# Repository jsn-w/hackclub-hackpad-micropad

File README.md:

# micropad!
This is a 12-key 'macro'pad with an OLED display and LEDs underneath the keys!
I plan on using this as a numberpad, with extra keys (calculator, gamebar).

# Schematic and PCB!

<p>These were made in KiCad. There are two layers in this PCB. The top serves as the signal plane while the bottom serves as the ground plane.</p>

# CAD
</p>Here is the assembled piece within AutoDesk Fusion 360! I was unable to find 3D models for the LEDs. The microcontroller also wouldn't export to Fusion360. Below I attached the KiCad PCB model and the Fusion360 model.</p>

</p>I separated the model into two pieces to print.</p>

# Parts Used
| Quantity | Item                      |
|---------|----------------------------|
| 1       | XIAO RP2040                |
| 1       | 3D printed case: base      |
| 1       | 3D printed case: cap       |
| 9       | SK6812MINI LEDs            |
| 12      | Cherry MX Switches         |
| 12      | DSA Keycaps                |
| 1       | 0.91" 128x32 OLED Display  |

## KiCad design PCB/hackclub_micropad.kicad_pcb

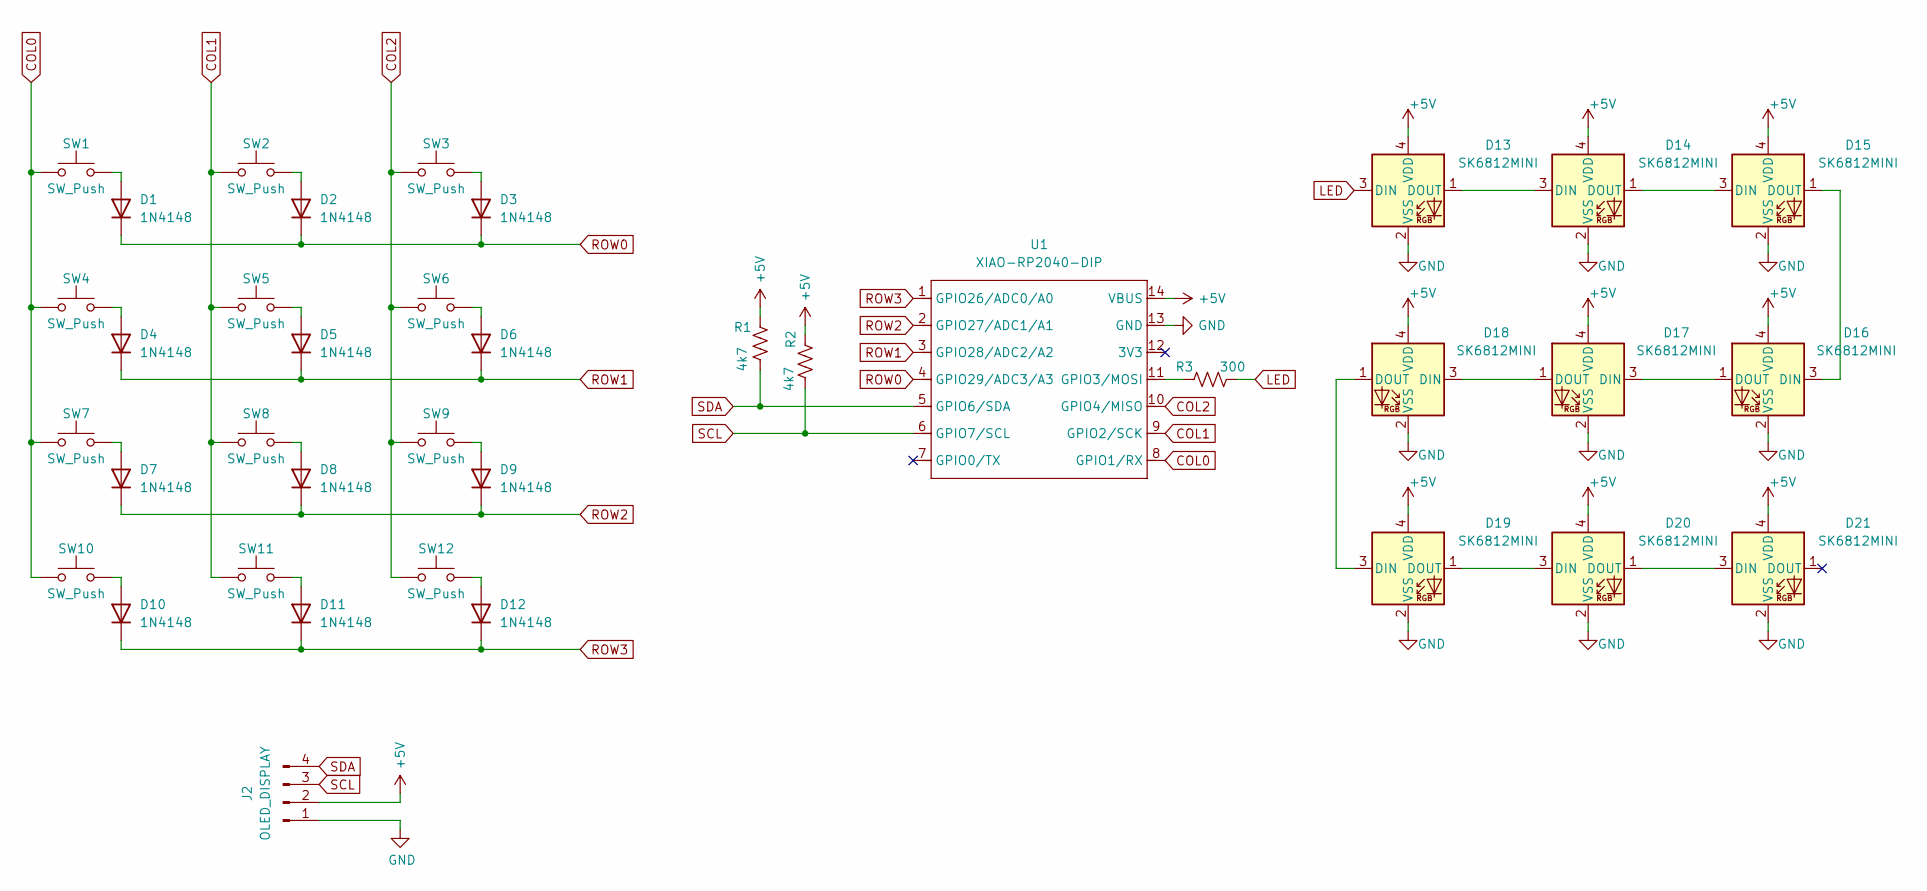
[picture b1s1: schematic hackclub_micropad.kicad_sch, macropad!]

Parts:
D1, D2, D3, D4, D5, D6, D7, D8, D9, D10, D11, D12: 1N4148; D_DO-35_SOD27_P7.62mm_Horizontal
D13, D14, D15, D16, D17, D18, D19, D20, D21: SK6812MINI; LED_SK6812MINI_PLCC4_3.5x3.5mm_P1.75mm
J2: OLED_DISPLAY; SSD1306-0.91-OLED-4pin-128x32
R1, R2: 4k7; R_0201_0603Metric_Pad0.64x0.40mm_HandSolder
R3: 300; R_0201_0603Metric_Pad0.64x0.40mm_HandSolder
SW1, SW2, SW3, SW4, SW5, SW6, SW7, SW8, SW9, SW10, SW11, SW12: SW_Push; SW_Cherry_MX_1.00u_PCB
U1: XIAO-RP2040-DIP

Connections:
+5V: D13.4 (VDD), D14.4 (VDD), D15.4 (VDD), D16.4 (VDD), D17.4 (VDD), D18.4 (VDD), D19.4 (VDD), D20.4 (VDD), D21.4 (VDD), J2.2, R1.1, R2.1, U1.14 (VBUS)
COL0: SW1.1, SW4.1, SW7.1, SW10.1, U1.8 (GPIO1/RX)
COL1: SW2.1, SW5.1, SW8.1, SW11.1, U1.9 (GPIO2/SCK)
COL2: SW3.1, SW6.1, SW9.1, SW12.1, U1.10 (GPIO4/MISO)
GND: D13.2 (VSS), D14.2 (VSS), D15.2 (VSS), D16.2 (VSS), D17.2 (VSS), D18.2 (VSS), D19.2 (VSS), D20.2 (VSS), D21.2 (VSS), J2.1, U1.13 (GND)
LED: D13.3 (DIN), R3.2
unnamed: D1.2 (A), SW1.2
unnamed: D2.2 (A), SW2.2
unnamed: D3.2 (A), SW3.2
unnamed: D4.2 (A), SW4.2
unnamed: D5.2 (A), SW5.2
unnamed: D6.2 (A), SW6.2
unnamed: D7.2 (A), SW7.2
unnamed: D8.2 (A), SW8.2
unnamed: D9.2 (A), SW9.2
unnamed: D10.2 (A), SW10.2
unnamed: D11.2 (A), SW11.2
unnamed: D12.2 (A), SW12.2
unnamed: D13.1 (DOUT), D14.3 (DIN)
unnamed: D14.1 (DOUT), D15.3 (DIN)
unnamed: D15.1 (DOUT), D16.3 (DIN)
unnamed: D16.1 (DOUT), D17.3 (DIN)
unnamed: D17.1 (DOUT), D18.3 (DIN)
unnamed: D18.1 (DOUT), D19.3 (DIN)
unnamed: D19.1 (DOUT), D20.3 (DIN)
unnamed: D20.1 (DOUT), D21.3 (DIN)
unnamed: R3.1, U1.11 (GPIO3/MOSI)
ROW0: D1.1 (K), D2.1 (K), D3.1 (K), U1.4 (GPIO29/ADC3/A3)
ROW1: D4.1 (K), D5.1 (K), D6.1 (K), U1.3 (GPIO28/ADC2/A2)
ROW2: D7.1 (K), D8.1 (K), D9.1 (K), U1.2 (GPIO27/ADC1/A1)
ROW3: D10.1 (K), D11.1 (K), D12.1 (K), U1.1 (GPIO26/ADC0/A0)
SCL: J2.3, R2.2, U1.6 (GPIO7/SCL)
SDA: J2.4, R1.2, U1.5 (GPIO6/SDA)

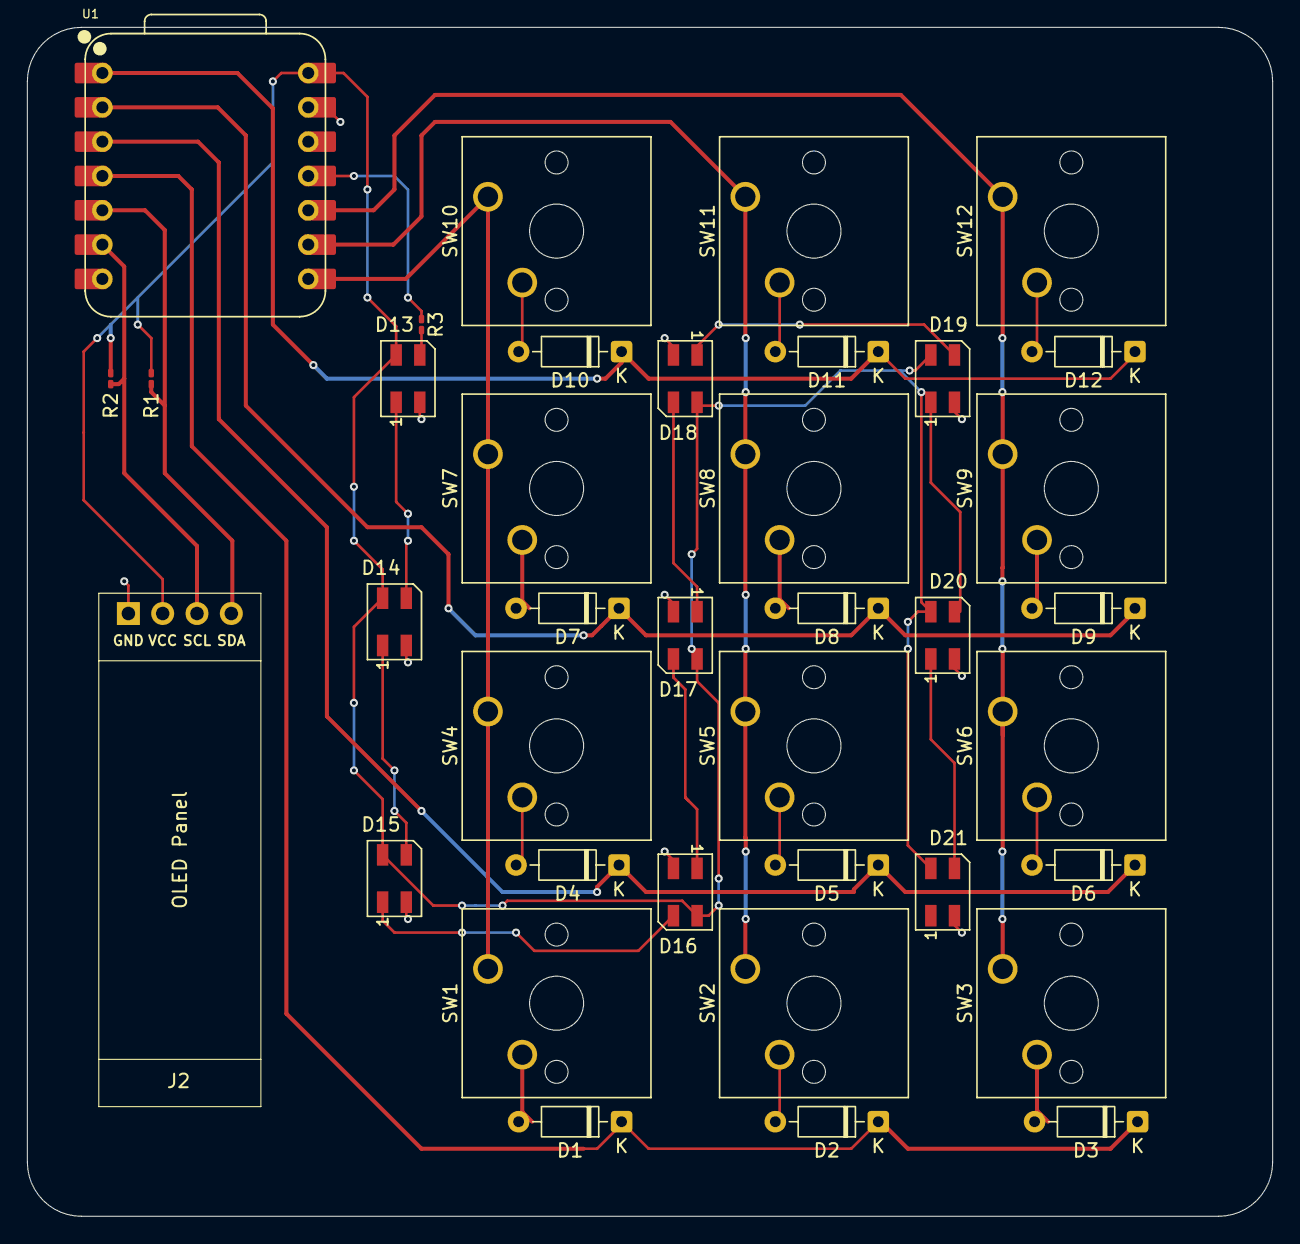
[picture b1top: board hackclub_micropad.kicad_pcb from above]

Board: 2 copper layers, 92.2 x 88.0 mm, 38 parts (0 on the bottom side), 33 nets.

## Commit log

2025-12-02 Create CAD
2025-12-02 Add project details for micropad in README
    Added detailed description of the micropad project including schematic, CAD images, and parts used.
2025-12-02 Updated step file for bottom layer
2025-12-02 Update images in README.md
    Updated images in the README with new dimensions and added a new image.
2025-12-02 Remove empty lines and fix OLED Display entry
2025-12-04 Revise README for micropad specifications
    Updated the micropad description and added details about the PCB layers and CAD models.
2025-12-04 Replace images in README with larger versions
    Updated image references for better visibility.
2025-12-04 Add HTML tags for improved README formatting
    Updated README to include HTML paragraph tags for better formatting.
